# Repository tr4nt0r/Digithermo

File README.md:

# Digithermo
Digital Thermometer

# BOM

Qty | Parts              | Value    | Device          | Package      | Description      |Vendor       |
----|--------------------|----------|-----------------|--------------|------------------|-------------|
1   |B1                  |MB6S      |Rectifier        |SOIC-4        |Bridge Rectifier  |[AliExpress](https://www.aliexpress.com/item/-/32838702658.html?spm=a2g0s.8937460.0.0.4f812e0eONVXqt)
1   |C1                  |100µ/16V  |Elko             |SMD 6.3x5.4mm |e.g. EEEFT1C101AR |[AliExpress](https://www.aliexpress.com/item/-/32911815415.html?spm=a2g0s.8937460.0.0.4f812e0eONVXqt)
1   |C2                  |10µ/16V   |Elko             |SMD 5x4mm     |e.g. EEEFK1C100AR |[AliExpress](https://www.aliexpress.com/item/Free-shiping-20pcs-16V-10UF-SMD-4x5mm-chip-Aluminum-Electrolytic-Capacitor/1342839445.html?spm=a2g0s.8937460.0.0.4f812e0eONVXqt)
1   |C3                  |100n      |Capacitor        |0603          |
1   |IC1                 |MEGA8     |Microcontroller  |TQFP32        |Atmel ATmega8A-AU|[AliExpress](https://www.aliexpress.com/item/-/32883046023.html?spm=a2g0s.8937460.0.0.4f812e0eONVXqt)
1   |IC4                 |7805      |Voltage regulator|DPAK/TO252    |L78M05CDT        |[AliExpress](https://www.aliexpress.com/item/20pcs-lot-New-78M05-TO252-7805-750mA-L78M05CDT-Three-terminal-voltage-regulator-tube/32818562902.html?spm=a2g0s.8937460.0.0.4f812e0eONVXqt)
4   |Q1,Q2,Q3,Q4         |BC847     |Transistor       |SOT23         |NPN Transistor   |[AliExpress](https://www.aliexpress.com/item/100pcs-BC847C-BC847-SOT-23-NPN-smd-transistor/32364894157.html?spm=a2g0s.8937460.0.0.4f812e0eONVXqt)
7   |R1,R2,R3,R4,R5,R6,R7|220       |Resistor         |0603          |
1   |R8                  |390       |Resistor         |0603          |
5   |R9,R10,R11,R12,R13  |4,7k      |Resistor         |0603          |
1   |R14                 |10k       |Resistor         |0603          |
4   |U1,U2,U3,U4         |          |7-Segment Display|              |0,56", Common Cathode|[AliExpress](https://www.aliexpress.com/item/-/32876326696.html?spm=a2g0s.8937460.0.0.4f812e0eONVXqt)
1   |J1                  |          |3.5mm Audio Jack |SMD           |e.g. PJ-328          |[AliExpress](https://www.aliexpress.com/item/10PCS-3-5mm-Female-Audio-Connector-5-Pin-SMT-SMD-Headphone-Jack-Socket-PJ-328/32828776775.html?spm=a2g0s.8937460.0.0.4f812e0eONVXqt)
1   |                    |          |3.5mm Audio Plug |              |                     |[AliExpress](https://de.aliexpress.com/item/10Pcs-lot-Plastic-metal-3-5mm-Male-Plug-Jack-Adapter-dual-channel-Audio-Connector-Male-Jack/32890263251.html?spm=a2g0s.9042311.0.0.542c4c4dyi8zH7)
1   |J2                  |          |DC Jack 2.1mm    |              |                     |[AliExpress](https://www.aliexpress.com/item/-/32902679494.html?spm=a2g0s.8937460.0.0.4f812e0eONVXqt)
1   |                    |DS18b20   |Temperaturfühler |              |                     |[AliExpress](https://www.aliexpress.com/item/Stainless-steel-package-Waterproof-DS18b20-temperature-probe-temperature-sensor-18B20-For-Arduino/32236998050.html?spm=a2g0s.8937460.0.0.4f812e0eONVXqt)

# Schematic

# Anschlüsse Temperaturfühler

Rot: VCC  
Schwarz: GND  
Gelb: DATA  

# Bilder

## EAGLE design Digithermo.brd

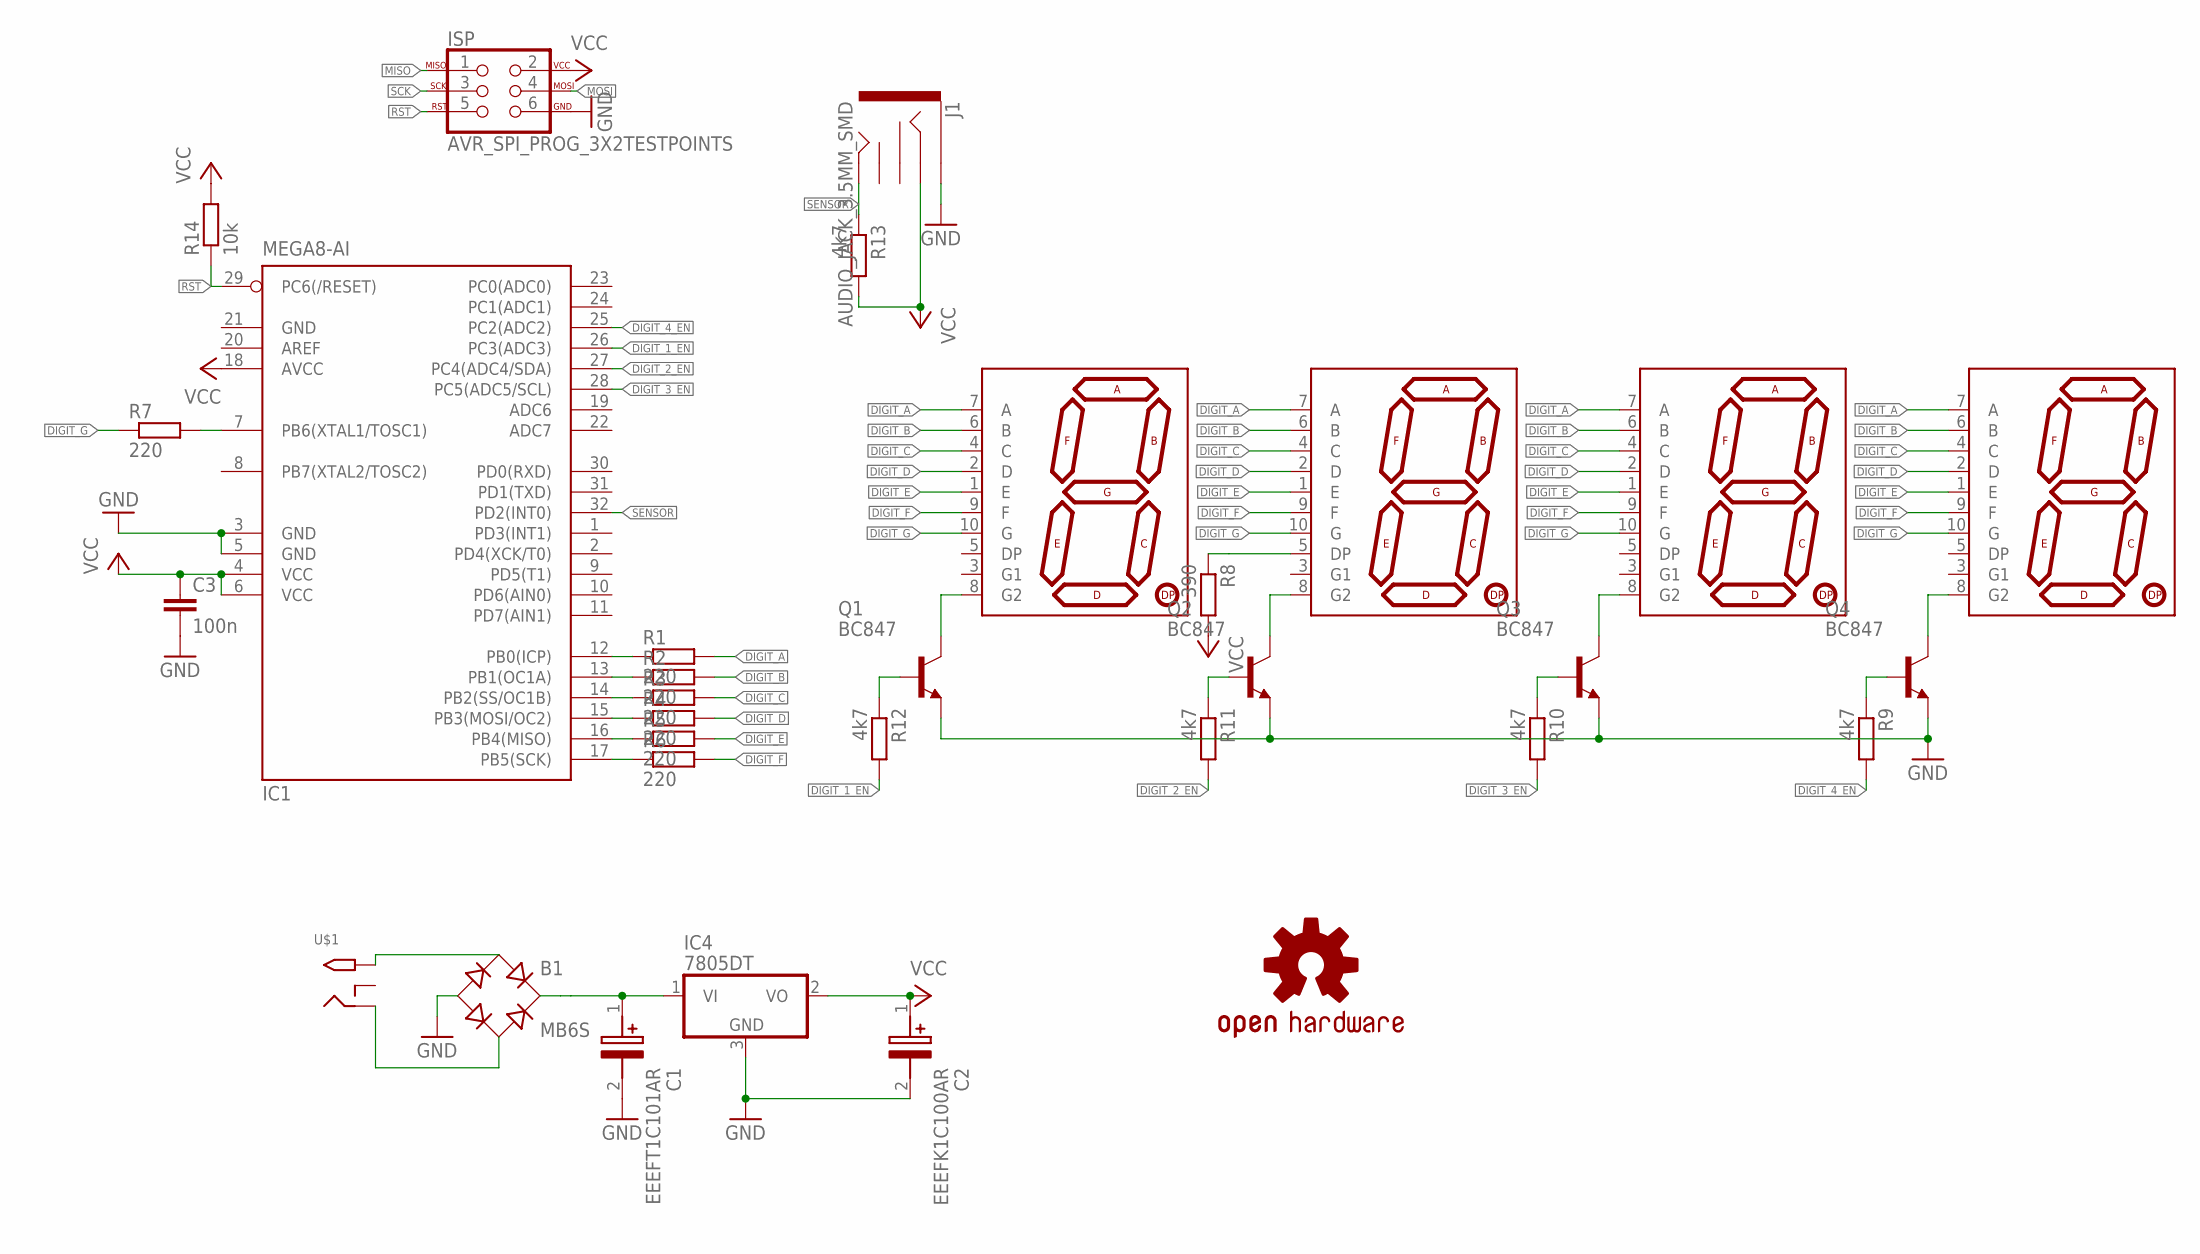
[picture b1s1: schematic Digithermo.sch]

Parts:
B1: MB6S; SOIC-4
C1: EEEFT1C101AR; HBV(C)
C2: EEEFK1C100AR; FKV(B)
C3: 100n; C0603
IC1: MEGA8-AI; TQFP32-08
IC4: 7805DT; TO252
ISP: AVR_SPI_PROG_3X2TESTPOINTS; 2X3_TEST_POINTS
J1: AUDIO_JACK_3.5MM_SMD; AUDIO-JACK-3.5MM-SMD
LOGO1: OSHW-LOGOL; OSHW-LOGO-L
Q1, Q2, Q3, Q4: BC847; SOT23
R1, R2, R3, R4, R5, R6, R7: 220; R0603
R8: 390; R0603
R9, R10, R11, R12, R13: 4k7; R0603
R14: 10k; R0603
U1, U2, U3, U4: 7-SEGMENT-DISPLAYPTH; 7-SEGMENT-DISPLAY
U$1: 2.1MMJACKTHM; PJ-102A

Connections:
DIGIT_1_EN: IC1.26 (PC3(ADC3)), R12.2
DIGIT_2_EN: IC1.27 (PC4(ADC4/SDA)), R11.2
DIGIT_3_EN: IC1.28 (PC5(ADC5/SCL)), R10.2
DIGIT_4_EN: IC1.25 (PC2(ADC2)), R9.2
DIGIT_A: R1.2, U1.7 (A), U2.7 (A), U3.7 (A), U4.7 (A)
DIGIT_B: R2.2, U1.6 (B), U2.6 (B), U3.6 (B), U4.6 (B)
DIGIT_C: R3.2, U1.4 (C), U2.4 (C), U3.4 (C), U4.4 (C)
DIGIT_D: R4.2, U1.2 (D), U2.2 (D), U3.2 (D), U4.2 (D)
DIGIT_E: R5.2, U1.1 (E), U2.1 (E), U3.1 (E), U4.1 (E)
DIGIT_F: R6.2, U1.9 (F), U2.9 (F), U3.9 (F), U4.9 (F)
DIGIT_G: R7.1, U1.10 (G), U2.10 (G), U3.10 (G), U4.10 (G)
GND: B1.-, C1.2 (-), C2.2 (-), C3.2, IC1.3 (GND), IC1.5 (GND), IC1.21 (GND), IC4.3 (GND), ISP.6, J1.SLEEVE, Q1.2 (E), Q2.2 (E), Q3.2 (E), Q4.2 (E)
MISO: IC1.16 (PB4(MISO)), ISP.1, R5.1
MOSI: IC1.15 (PB3(MOSI/OC2)), ISP.4, R4.1
unnamed: B1.~1 (AC1), U$1.TIP
unnamed: B1.~2 (AC2), U$1.RING
unnamed: B1.+, C1.1 (+), IC4.1 (VI)
unnamed: IC1.7 (PB6(XTAL1/TOSC1)), R7.2
unnamed: Q1.3 (C), U1.8 (G2)
unnamed: R8.1, U2.5 (DP)
unnamed: IC1.14 (PB2(SS/OC1B)), R3.1
unnamed: IC1.13 (PB1(OC1A)), R2.1
unnamed: IC1.12 (PB0(ICP)), R1.1
unnamed: Q1.1 (B), R12.1
unnamed: Q2.3 (C), U2.8 (G2)
unnamed: Q2.1 (B), R11.1
unnamed: Q3.3 (C), U3.8 (G2)
unnamed: Q3.1 (B), R10.1
unnamed: Q4.3 (C), U4.8 (G2)
unnamed: Q4.1 (B), R9.1
RST: IC1.29 (PC6(/RESET)), ISP.5, R14.1
SCK: IC1.17 (PB5(SCK)), ISP.3, R6.1
SENSOR: IC1.32 (PD2(INT0)), J1.TIP, R13.1
VCC: C2.1 (+), C3.1, IC1.4 (VCC), IC1.6 (VCC), IC1.18 (AVCC), IC4.2 (VO), ISP.2, J1.RING, R8.2, R13.2, R14.2

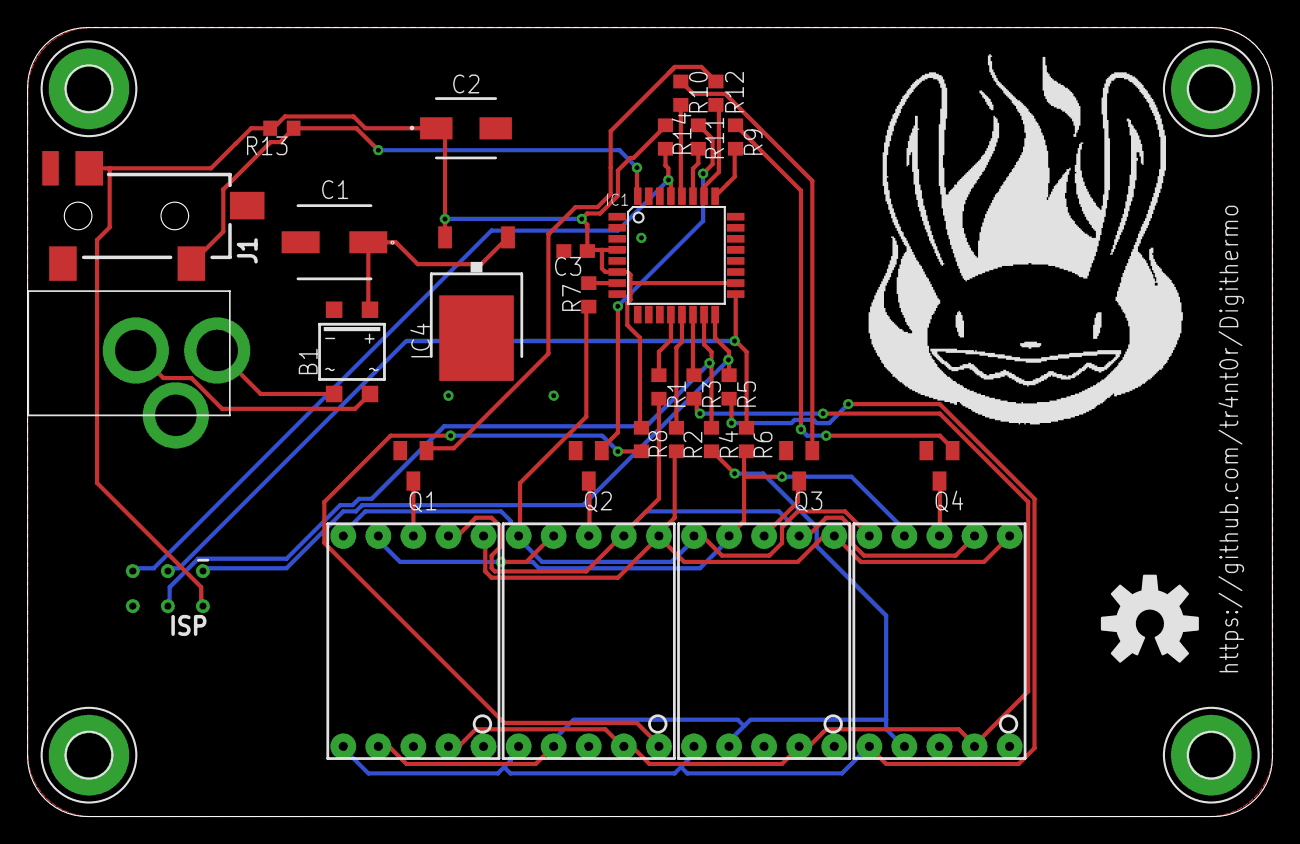
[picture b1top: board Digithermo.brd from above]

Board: 2 copper layers, 90.2 x 57.1 mm, 36 parts (0 on the bottom side), 34 nets.

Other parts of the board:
E$1, E$2, E$3, E$4: 3,2-PAD

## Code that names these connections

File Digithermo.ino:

// Beware of bugs in the code; I have only proved it correct, not tried it.

#include <TimerOne.h>
#include <DallasTemperature.h>
#include <OneWire.h>

const uint8_t numbers[10] = { 0x3F, 0x06, 0x5B, 0x4F, 0x66, 0x6D, 0x7D, 0x07, 0x7F, 0x6f };
const uint8_t letter_E = 0x79;
const uint8_t letter_r = 0x50;
const uint8_t symbol_minus = 0x40;

const uint8_t digit2pin[4] = { 16, 19, 18, 17 };
const uint8_t SENSOR_PIN = 2;
uint8_t active = 0;
uint8_t digit = 0;
volatile int16_t temperature;
volatile bool sensorError = false;

OneWire wire(SENSOR_PIN);
DallasTemperature sensors(&wire);

void setup()
{
	DDRB = 0xFF; //set PB0 - PB6 as Output
	DDRC = 0xFF; //set PC2 - PC5 as Output

	Timer1.initialize(5000);
	Timer1.attachInterrupt(displayMultiplex);	
	selftest();
	sensors.begin();
}

void loop()
{
	//wait for sensor to connect
	while (!sensors.requestTemperaturesByIndex(0)) {
		sensorError = true;
		delay(1000);
	}
	sensorError = false;
	noInterrupts();
	temperature = (int16_t)(sensors.getTempCByIndex(0) * 10.0);
	interrupts();
	delay(1000);
}

void selftest() {
	//7-segment display selftest
	uint8_t i = 10;
	while (i-- > 0) {
		temperature = 1111 * i;
		delay(50000);
	}
}


void displayMultiplex() {
	digitalWrite(digit2pin[active], LOW);  //disable last digit
	active = (active == 3) ? 0 : active + 1; //go to next digit
	digitalWrite(digit2pin[active], HIGH); //enable next digit
	PORTB = 0;
	if (!sensorError) {

		if (temperature < 0 && active == 3) {
			PORTB = symbol_minus;
		}
		else if (abs(temperature) < pow(10, active) && active > 1){  //don't display leading zero
			PORTB = 0;
		} else {
			digit = abs(temperature) / pow(10, active) % 10;  //get number to display on active digit
			PORTB = numbers[digit];  //Set I/Os for digit
		}
	} else {
		//display Err 
		switch (active) {
		case 0:
			PORTB = 0x00; //Digit off			
			break;
		case 3:
			PORTB = letter_E;
			break;
		case 2:
		case 1:
			PORTB = letter_r;
			break;
		}
	}
}

int32_t pow(int base, int exp) {
	int32_t result = 1;
	for (;;) {
		if (exp & 1)
			result *= base;
		exp >>= 1;
		if (!exp)
			break;
		base *= base;
	}

	return result;
}

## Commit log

2018-09-09 added image of pcb front
2018-09-09 Added BOM to README.md
2018-09-12 Eckenrundungen geändert
2018-09-12 added schematic image
2018-09-26 First commit of firmware
    Beware of bugs in the code; I have only proved it correct, not tried it!
2018-09-27 Fixed Pinout settings
2018-09-27 changed define to const
2018-10-09 fixed a bug
2018-10-12 Added image
2018-10-12 convertet image to jpg
2018-10-12 removed image
2018-10-12 Bild verkleinert
2018-10-12 Added photo
2018-10-24 reduced to 1 decimal, added sign for negative values
2019-12-19 major changes, first working version

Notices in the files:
parts and their libraries:
SparkFun-Connectors: Licensing: Creative Commons ShareAlike 4.0 International - https://creativecommons.org/licenses/by-sa/4.0
